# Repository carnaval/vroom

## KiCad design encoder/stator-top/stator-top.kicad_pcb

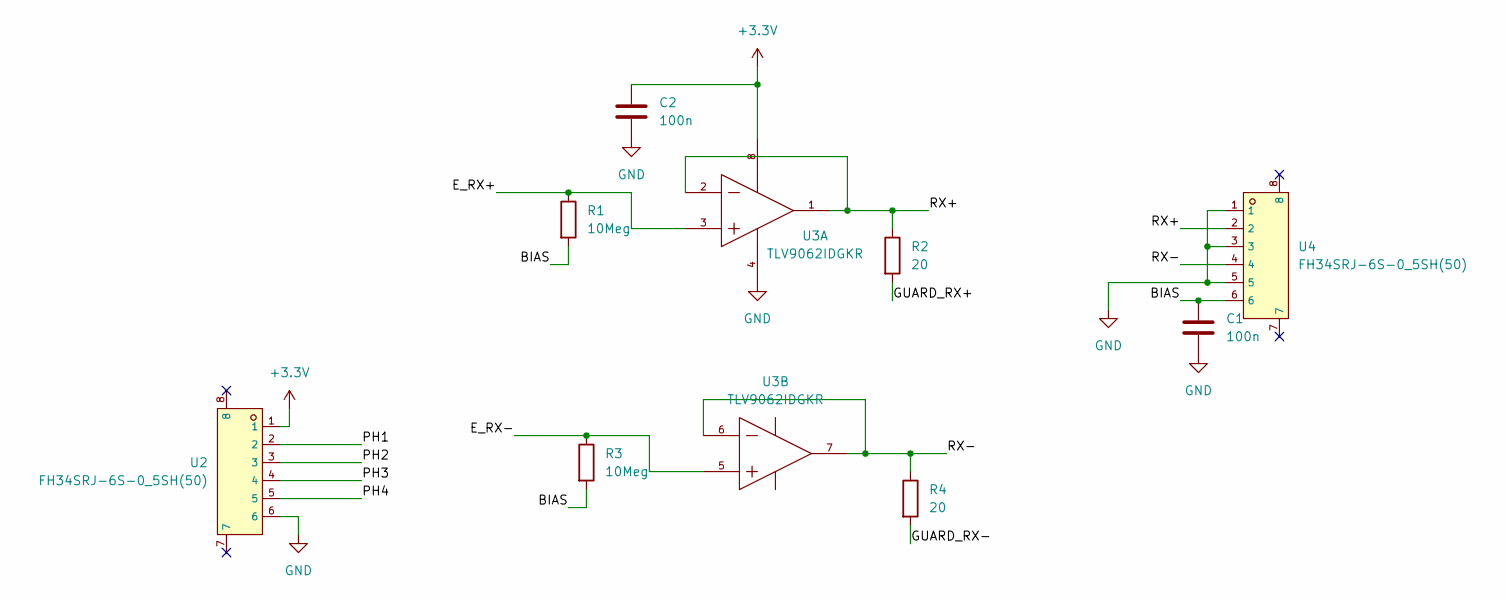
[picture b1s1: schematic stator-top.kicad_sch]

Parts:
C1, C2: 100n; C_0603_1608Metric
R1, R3: 10Meg; R_0603_1608Metric
R2, R4: 20; R_0603_1608Metric
U2, U4: FH34SRJ-6S-0_5SH(50); FFC-SMD_6P-P0.50_FH34SRJ-6S-0.5SH; LCSC C224194
U3: TLV9062IDGKR; VSSOP-8_L3.0-W3.0-P0.65-LS4.9-BL; LCSC C398356

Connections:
+3.3V: C2.1, U2.1, U3.8 (V+)
/<NO NET>: U2.2
/BIAS: C1.1, R1.2, R3.2, U4.6
/E_RX+: R1.1, U3.3 (IN1+)
/E_RX-: R3.1, U3.5 (IN2+)
/GUARD_RX+: R2.2
/GUARD_RX-: R4.2
/PH2: U2.3
/PH3: U2.4
/PH4: U2.5
/RX+: R2.1, U3.1 (OUT1), U3.2 (IN1-), U4.2
/RX-: R4.1, U3.6 (IN2-), U3.7 (OUT2), U4.4
GND: C1.2, C2.2, U2.6, U3.4 (V-), U4.1, U4.3, U4.5

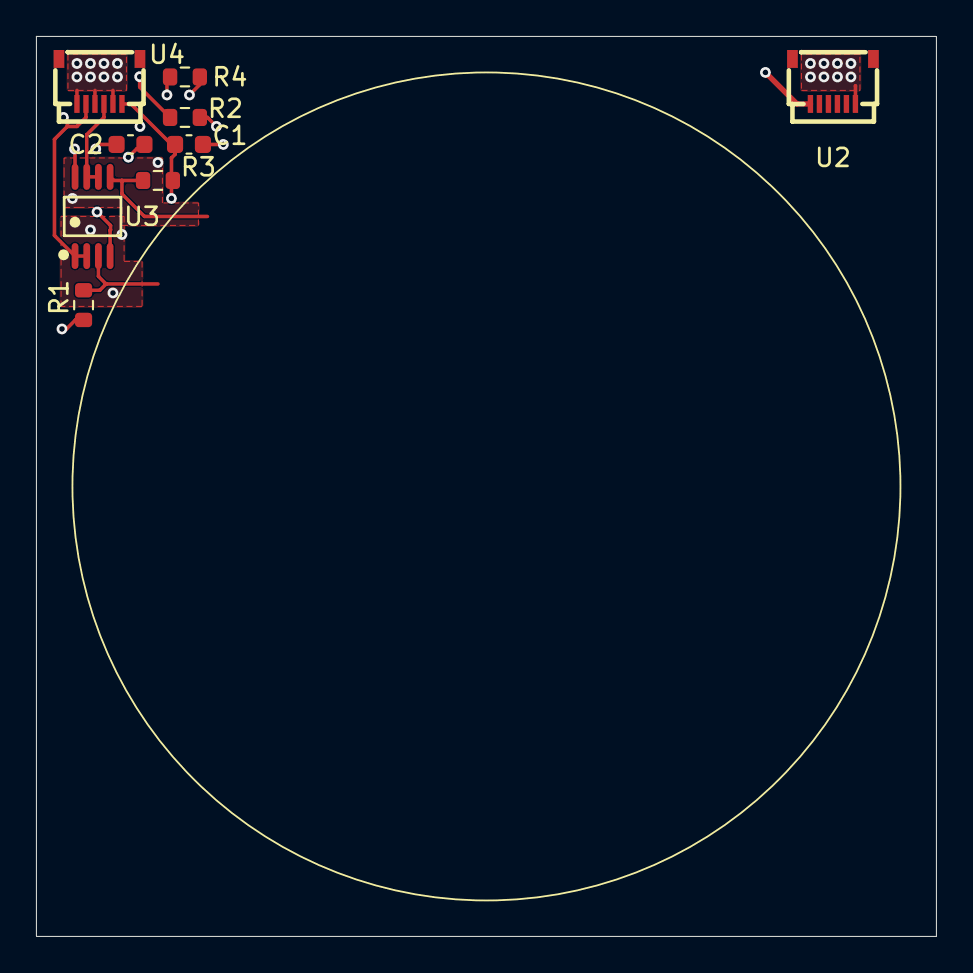
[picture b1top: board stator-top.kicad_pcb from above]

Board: 4 copper layers, 50.0 x 50.0 mm, 9 parts (0 on the bottom side), 7 nets.

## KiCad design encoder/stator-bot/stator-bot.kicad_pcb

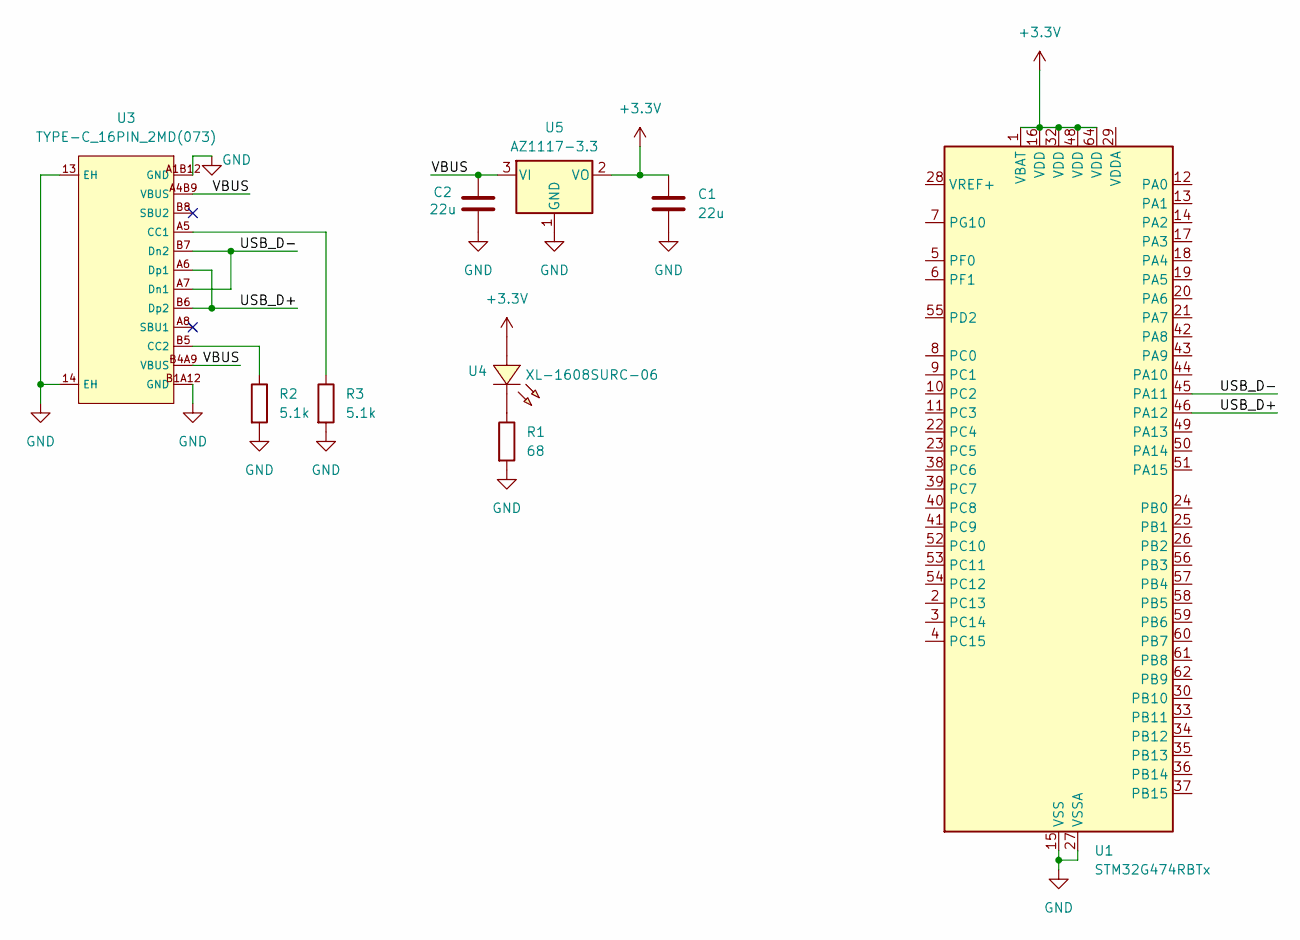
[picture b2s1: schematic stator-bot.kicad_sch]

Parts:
C1, C2: 22u; C_0805_2012Metric
R1: 68; R_0603_1608Metric
R2, R3: 5.1k; R_0603_1608Metric
U1: STM32G474RBTx; LQFP-64_10x10mm_P0.5mm
U3: TYPE-C_16PIN_2MD(073); USB-C-SMD_TYPE-C-16PIN-2MD-073; LCSC C2765186
U4: XL-1608SURC-06; LED0603-RD_RED; LCSC C965799
U5: AZ1117-3.3; SOT-223-3_TabPin2

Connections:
+3.3V: C1.1, U1.1 (VBAT), U1.16 (VDD), U1.32 (VDD), U1.48 (VDD), U1.64 (VDD), U4.2 (A), U5.2 (VO)
/USB_D+: U1.46 (PA12), U3.A6 (Dp1), U3.B6 (Dp2)
/USB_D-: U1.45 (PA11), U3.A7 (Dn1), U3.B7 (Dn2)
/VBUS: C2.1, U3.A4B9 (VBUS), U3.B4A9 (VBUS), U5.3 (VI)
GND: C1.2, C2.2, R1.2, R2.2, R3.2, U1.15 (VSS), U1.27 (VSSA), U1.31 (VSS), U1.47 (VSS), U1.63 (VSS), U3.13 (EH), U3.14 (EH), U3.A1B12 (GND), U3.B1A12 (GND), U5.1 (GND)
unnamed: R3.1, U3.A5 (CC1)
unnamed: R2.1, U3.B5 (CC2)
unnamed: R1.1, U4.1 (K)

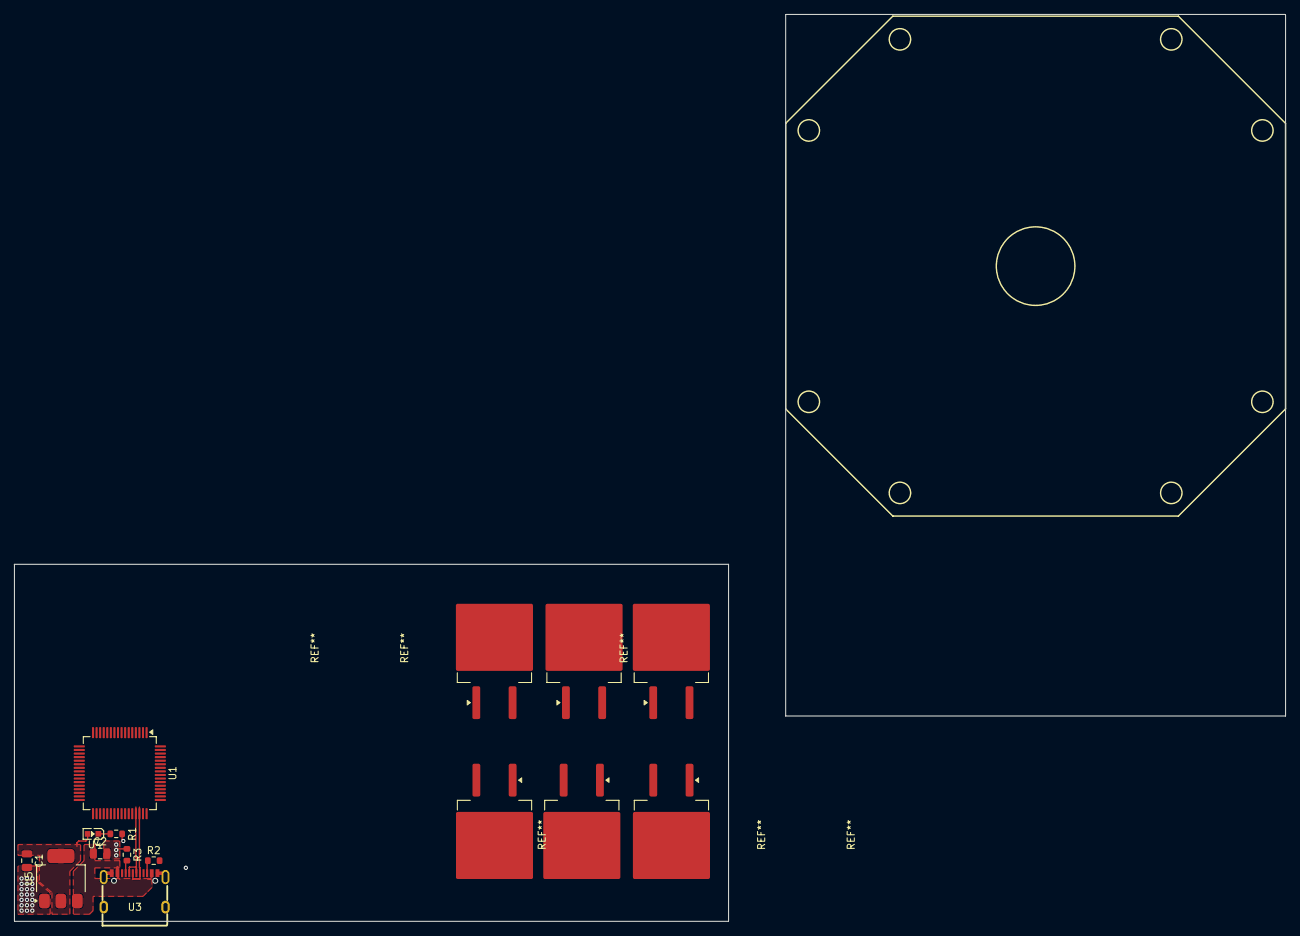
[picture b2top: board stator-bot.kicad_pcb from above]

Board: 4 copper layers, 100.0 x 50.0 mm, 9 parts (0 on the bottom side), 8 nets.
